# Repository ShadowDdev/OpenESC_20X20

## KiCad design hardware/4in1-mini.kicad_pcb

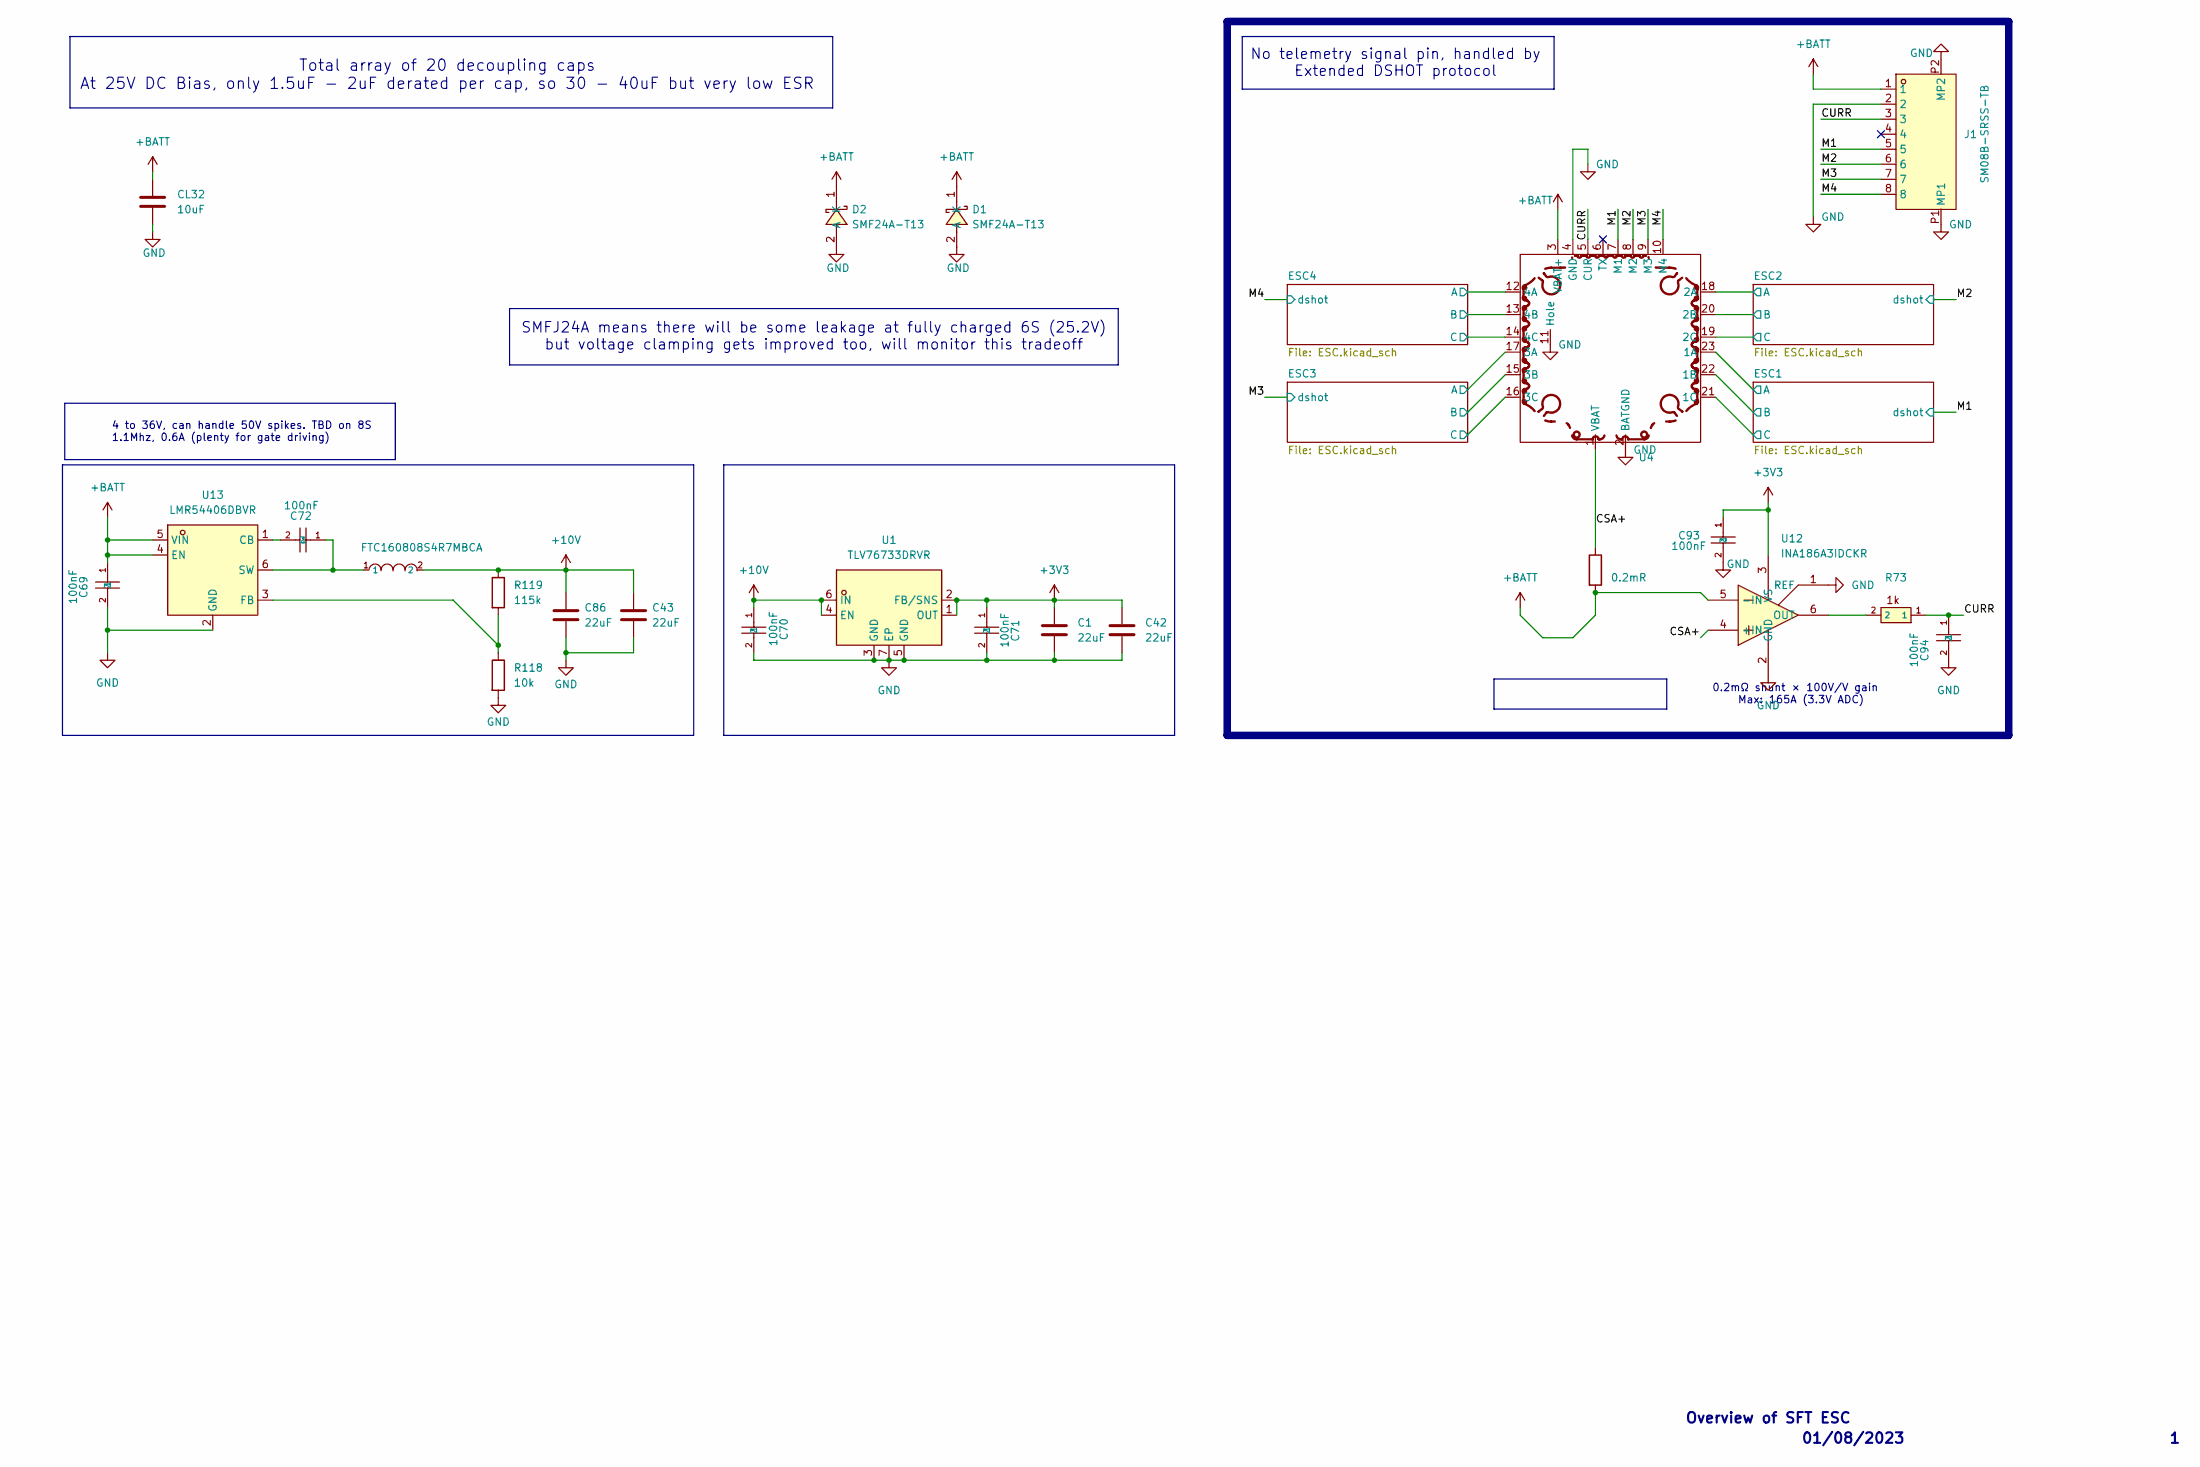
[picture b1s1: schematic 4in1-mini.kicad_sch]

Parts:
C1, C42: 22uF; C_0402_1005Metric; MPN CL05A226MQ5QUNC; LCSC C105226
C43, C86: 22uF; C_0603_1608Metric; MPN CL10A226MO7JZNC; LCSC C2762594
C69, C70, C71, C72, C93, C94: 100nF; C_0201_0603Metric; MPN GRM033R6YA104KE14D; LCSC C181043
CL32: 10uF; C_1206_3216Metric; MPN CL31B106KBHNNNE; LCSC C89632
D1, D2: SMF24A-T13; SOD-123FL_L2.7-W1.8-LS3.7-RD; MPN SMF24A-T13; LCSC Part C1977154
J1: SM08B-SRSS-TB; JST_SM08B-SRSS-TB; MPN SM08B-SRSS-TB(LF)(SN); LCSC C160407
R73: 1k; R_0201_0603Metric; MPN 0201WMF1001TEE; LCSC C270365
R118: 10k; R_0201_0603Metric; MPN RC0201FR-0710KL; LCSC C106225
R119: 115k; R_0201_0603Metric; MPN RTT011153FTH; LCSC C166378
Rsense1: 0.2mR; R_2512_6332Metric; MPN ASR-S-3-0.2F; LCSC C695806
U1: TLV76733DRVR; WSON-6_L2.0-W2.0-P0.65-TL-EP; MPN TLV76733DRVR; LCSC C2848334
U4: 4in1ESC
U5: FTC160808S4R7MBCA; IND-SMD_L1.6-W0.8_FTC160865SR47MBCA; MPN FTC160808S4R7MBCA; LCSC C46594347
U12: INA186A3IDCKR; SOT-363_SC-70-6; MPN INA186A3IDCKR; LCSC C2058245
U13: LMR54406DBVR; SOT-23-6_L2.9-W1.6-P0.95-LS2.8-BR; MPN LMR54406DBVR; LCSC Part C5219316

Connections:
+3V3: C1.2, C42.2, C71.1, C93.1, U1.1 (OUT), U1.2 (FB/SNS), U12.3 (VS); also elsewhere on the board
+10V: C43.1, C70.1, C86.1, R119.1, U1.4 (EN), U1.6 (IN), U5.2; also elsewhere on the board
+BATT: C69.1, CL32.1, D1.1 (K), D2.1 (K), J1.1, Rsense1.2, U4.3 (VBAT+), U12.5 (-IN), U13.4 (EN), U13.5 (VIN); also elsewhere on the board
/CSA+: Rsense1.1, U4.1 (VBAT), U12.4 (+IN)
/CURR: C94.1, J1.3, R73.1, U4.5 (CUR)
/ESC1/MotorA: U4.23 (1A); also elsewhere on the board
/ESC1/MotorB: U4.22 (1B); also elsewhere on the board
/ESC1/MotorC: U4.21 (1C); also elsewhere on the board
/ESC2/MotorA: U4.18 (2A); also elsewhere on the board
/ESC2/MotorB: U4.20 (2B); also elsewhere on the board
/ESC2/MotorC: U4.19 (2C); also elsewhere on the board
/ESC3/MotorA: U4.17 (3A); also elsewhere on the board
/ESC3/MotorB: U4.15 (3B); also elsewhere on the board
/ESC3/MotorC: U4.16 (3C); also elsewhere on the board
/ESC4/MotorA: U4.12 (4A); also elsewhere on the board
/ESC4/MotorB: U4.13 (4B); also elsewhere on the board
/ESC4/MotorC: U4.14 (4C); also elsewhere on the board
/M1: J1.5, U4.7 (M1); also elsewhere on the board
/M2: J1.6, U4.8 (M2); also elsewhere on the board
/M3: J1.7, U4.9 (M3); also elsewhere on the board
/M4: J1.8, U4.10 (M4); also elsewhere on the board
GND: C1.1, C42.1, C43.2, C69.2, C70.2, C71.2, C86.2, C93.2, C94.2, CL32.2, D1.2 (A), D2.2 (A), J1.2, J1.P1 (MP1), J1.P2 (MP2), R118.2, U1.3 (GND), U1.5 (GND), U1.7 (EP), U4.2 (BATGND), U4.4 (GND), U4.11 (Hole), U12.1 (REF), U12.2 (GND), U13.2 (GND); also elsewhere on the board
unnamed: R73.2, U12.6 (OUT)
unnamed: C72.2, U13.1 (CB)
unnamed: R118.1, R119.2, U13.3 (FB)
unnamed: C72.1, U5.1, U13.6 (SW)

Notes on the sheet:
01/08/2023
No telemetry signal pin, handled by Extended DSHOT protocol
4 to 36V, can handle 50V spikes. TBD on 8S 1.1Mhz, 0.6A (plenty for gate driving)
SMFJ24A means there will be some leakage at fully charged 6S (25.2V) but voltage clamping gets improved too, will monitor this tradeoff
Overview of SFT ESC
Total array of 20 decoupling caps At 25V DC Bias, only 1.5uF - 2uF derated per cap, so 30 - 40uF but very low ESR
0.2mΩ shunt × 100V/V gain Max: 165A (3.3V ADC)

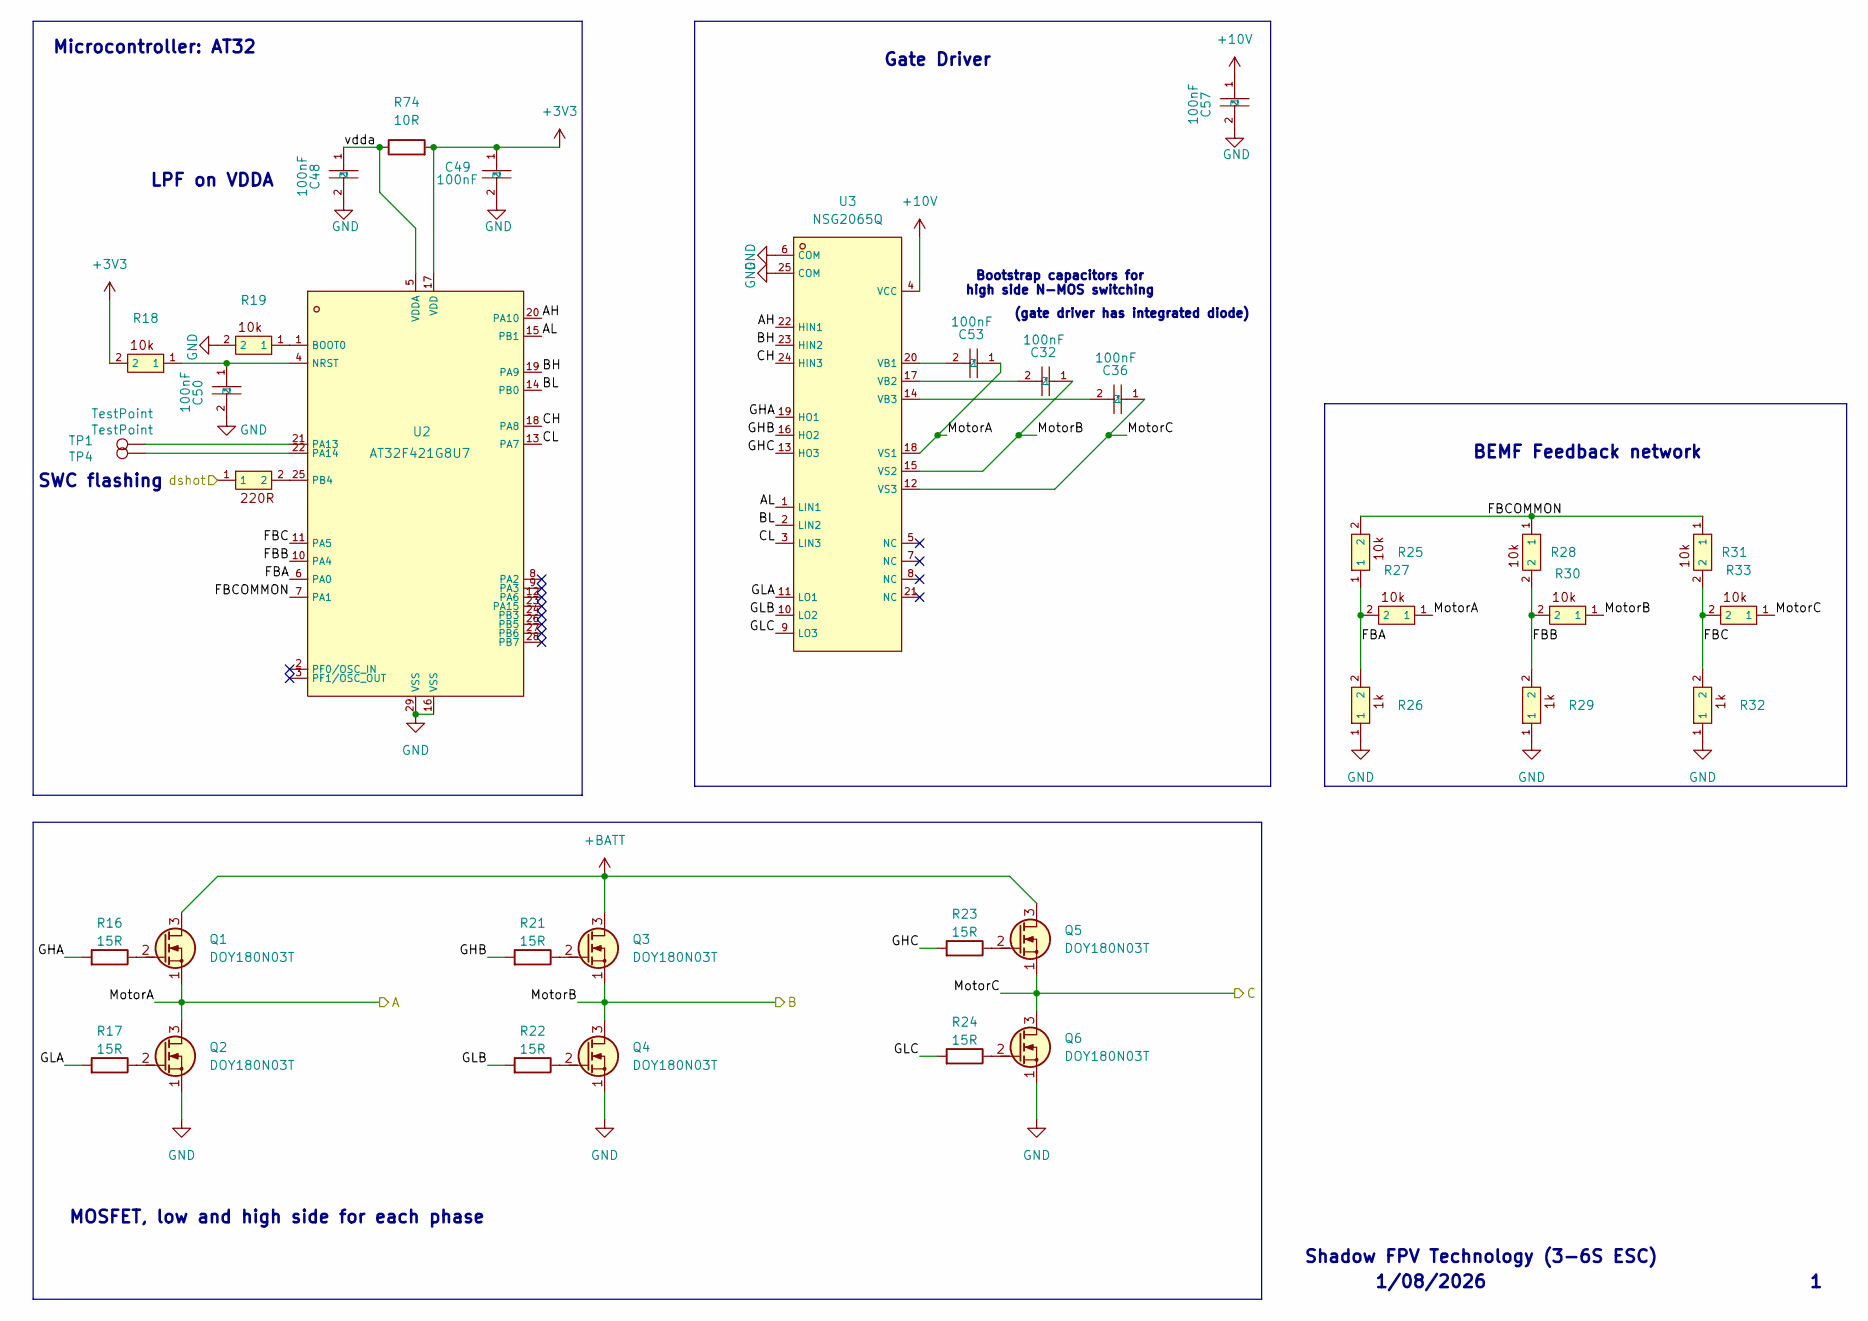
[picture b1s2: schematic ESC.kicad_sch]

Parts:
C32, C36, C53: 100nF; C_0402_WIDE; MPN CL05B104KB54PNC; LCSC C307331
C48, C49, C50, C57: 100nF; C_0201_0603Metric; MPN GRM033R6YA104KE14D; LCSC C181043
Q1, Q2, Q3, Q4, Q5, Q6: DOY180N03T; Diodes_PowerDI3333-8; MPN DOY180N03T; LCSC C49441966
R16, R17, R21, R22, R23, R24: 15R; R_0201_0603Metric; MPN 0201WMF150JTEE; LCSC C473542
R18, R19, R25, R27, R28, R30, R31, R33: 10k; R_0201_0603Metric; MPN RC0201FR-0710KL; LCSC C106225
R20: 220R; R_0201_0603Metric; MPN AC0201FR-07220RL; LCSC C226468
R26, R29, R32: 1k; R_0201_0603Metric; MPN 0201WMF1001TEE; LCSC C270365
R74: 10R; R_0201_0603Metric; MPN RC0201FR-0710RL; LCSC C106226
TP1, TP4: TestPoint; TestPoint_Pad_D1.0mm
U2: AT32F421G8U7; QFN-28_L4.0-W4.0-P0.40-TL-EP2.4; MPN AT32F421G8U7; LCSC C2765098
U3: NSG2065Q; QFN-24_L4.0-W4.0-P0.50-TL-EP2.8; MPN NSG2065Q; LCSC C41414478

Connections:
+3V3: C49.1, R18.2, R74.2, U2.17 (VDD); also elsewhere on the board
+10V: C57.1, U3.4 (VCC); also elsewhere on the board
+BATT: Q1.3 (D), Q3.3 (D), Q5.3 (D); also elsewhere on the board
/ESC1/AH: U2.20 (PA10), U3.22 (HIN1)
/ESC1/AL: U2.15 (PB1), U3.1 (LIN1)
/ESC1/BH: U2.19 (PA9), U3.23 (HIN2)
/ESC1/BL: U2.14 (PB0), U3.2 (LIN2)
/ESC1/CH: U2.18 (PA8), U3.24 (HIN3)
/ESC1/CL: U2.13 (PA7), U3.3 (LIN3)
/ESC1/FBA: R25.1, R26.2, R27.2, U2.6 (PA0)
/ESC1/FBB: R28.2, R29.2, R30.2, U2.10 (PA4)
/ESC1/FBC: R31.2, R32.2, R33.2, U2.11 (PA5)
/ESC1/FBCOMMON: R25.2, R28.1, R31.1, U2.7 (PA1)
/ESC1/GHA: R16.1, U3.19 (HO1)
/ESC1/GHB: R21.1, U3.16 (HO2)
/ESC1/GHC: R23.1, U3.13 (HO3)
/ESC1/GLA: R17.1, U3.11 (LO1)
/ESC1/GLB: R22.1, U3.10 (LO2)
/ESC1/GLC: R24.1, U3.9 (LO3)
/ESC1/MotorA: C53.1, Q1.1 (S), Q2.3 (D), R27.1, U3.18 (VS1); also elsewhere on the board
/ESC1/MotorB: C32.1, Q3.1 (S), Q4.3 (D), R30.1, U3.15 (VS2); also elsewhere on the board
/ESC1/MotorC: C36.1, Q5.1 (S), Q6.3 (D), R33.1, U3.12 (VS3); also elsewhere on the board
/ESC1/vdda: C48.1, R74.1, U2.5 (VDDA)
/M1: R20.1; also elsewhere on the board
GND: C48.2, C49.2, C50.2, C57.2, Q2.1 (S), Q4.1 (S), Q6.1 (S), R19.2, R26.1, R29.1, R32.1, U2.16 (VSS), U2.29 (VSS), U3.6 (COM), U3.25 (COM); also elsewhere on the board
unnamed: Q1.2 (G), R16.2
unnamed: Q2.2 (G), R17.2
unnamed: Q3.2 (G), R21.2
unnamed: Q4.2 (G), R22.2
unnamed: Q5.2 (G), R23.2
unnamed: Q6.2 (G), R24.2
unnamed: R19.1, U2.1 (BOOT0)
unnamed: C50.1, R18.1, U2.4 (NRST)
unnamed: TP1.1 (1_1), U2.21 (PA13)
unnamed: TP4.1 (1_1), U2.22 (PA14)
unnamed: R20.2, U2.25 (PB4)
unnamed: C53.2, U3.20 (VB1)
unnamed: C32.2, U3.17 (VB2)
unnamed: C36.2, U3.14 (VB3)

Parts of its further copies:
C33, C34, C35, C37, C38, C39, C59, C73, C83: 100nF; C_0402_WIDE; MPN CL05B104KB54PNC; LCSC C307331
C44, C45, C46, C63, C64, C65, C66, C77, C78, C79, C80, C88: 100nF; C_0201_0603Metric; MPN GRM033R6YA104KE14D; LCSC C181043
Q7, Q8, Q9, Q10, Q11, Q12, Q13, Q14, Q15, Q16, Q17, Q18, Q19, Q20, Q21, Q22, Q23, Q24: DOY180N03T; Diodes_PowerDI3333-8; MPN DOY180N03T; LCSC C49441966
R1, R2, R6, R7, R8, R9, R37, R38, R42, R43, R44, R45, R55, R56, R60, R61, R62, R63: 15R; R_0201_0603Metric; MPN 0201WMF150JTEE; LCSC C473542
R3, R4, R10, R12, R13, R15, R34, R36, R39, R40, R46, R48, R49, R51, R52, R54, R57, R58, R64, R66, R67, R69, R70, R72: 10k; R_0201_0603Metric; MPN RC0201FR-0710KL; LCSC C106225
R5, R41, R59: 220R; R_0201_0603Metric; MPN AC0201FR-07220RL; LCSC C226468
R11, R14, R35, R47, R50, R53, R65, R68, R71: 1k; R_0201_0603Metric; MPN 0201WMF1001TEE; LCSC C270365
R75, R76, R77: 10R; R_0201_0603Metric; MPN RC0201FR-0710RL; LCSC C106226
TP2, TP3, TP5, TP6, TP7, TP8: TestPoint; TestPoint_Pad_D1.0mm
U6, U8, U10: AT32F421G8U7; QFN-28_L4.0-W4.0-P0.40-TL-EP2.4; MPN AT32F421G8U7; LCSC C2765098
U7, U9, U11: NSG2065Q; QFN-24_L4.0-W4.0-P0.50-TL-EP2.8; MPN NSG2065Q; LCSC C41414478

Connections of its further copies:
+3V3: C45.1, C65.1, C79.1, R3.2, R39.2, R57.2, R75.2, R76.2, R77.2, U6.17 (VDD), U8.17 (VDD), U10.17 (VDD); also elsewhere on the board
+10V: C63.1, C77.1, C88.1, U7.4 (VCC), U9.4 (VCC), U11.4 (VCC); also elsewhere on the board
+BATT: Q7.3 (D), Q9.3 (D), Q11.3 (D), Q13.3 (D), Q15.3 (D), Q17.3 (D), Q19.3 (D), Q21.3 (D), Q23.3 (D); also elsewhere on the board
/ESC2/AH: U6.20 (PA10), U7.22 (HIN1)
/ESC2/AL: U6.15 (PB1), U7.1 (LIN1)
/ESC2/BH: U6.19 (PA9), U7.23 (HIN2)
/ESC2/BL: U6.14 (PB0), U7.2 (LIN2)
/ESC2/CH: U6.18 (PA8), U7.24 (HIN3)
/ESC2/CL: U6.13 (PA7), U7.3 (LIN3)
/ESC2/FBA: R10.1, R11.2, R12.2, U6.6 (PA0)
/ESC2/FBB: R13.2, R14.2, R15.2, U6.10 (PA4)
/ESC2/FBC: R34.2, R35.2, R36.2, U6.11 (PA5)
/ESC2/FBCOMMON: R10.2, R13.1, R34.1, U6.7 (PA1)
/ESC2/GHA: R1.1, U7.19 (HO1)
/ESC2/GHB: R6.1, U7.16 (HO2)
/ESC2/GHC: R8.1, U7.13 (HO3)
/ESC2/GLA: R2.1, U7.11 (LO1)
/ESC2/GLB: R7.1, U7.10 (LO2)
/ESC2/GLC: R9.1, U7.9 (LO3)
/ESC2/MotorA: C59.1, Q7.1 (S), Q8.3 (D), R12.1, U7.18 (VS1); also elsewhere on the board
/ESC2/MotorB: C33.1, Q9.1 (S), Q10.3 (D), R15.1, U7.15 (VS2); also elsewhere on the board
/ESC2/MotorC: C37.1, Q11.1 (S), Q12.3 (D), R36.1, U7.12 (VS3); also elsewhere on the board
/ESC2/vdda: C44.1, R75.1, U6.5 (VDDA)
/ESC3/AH: U8.20 (PA10), U9.22 (HIN1)
/ESC3/AL: U8.15 (PB1), U9.1 (LIN1)
/ESC3/BH: U8.19 (PA9), U9.23 (HIN2)
/ESC3/BL: U8.14 (PB0), U9.2 (LIN2)
/ESC3/CH: U8.18 (PA8), U9.24 (HIN3)
/ESC3/CL: U8.13 (PA7), U9.3 (LIN3)
/ESC3/FBA: R46.1, R47.2, R48.2, U8.6 (PA0)
/ESC3/FBB: R49.2, R50.2, R51.2, U8.10 (PA4)
/ESC3/FBC: R52.2, R53.2, R54.2, U8.11 (PA5)
/ESC3/FBCOMMON: R46.2, R49.1, R52.1, U8.7 (PA1)
/ESC3/GHA: R37.1, U9.19 (HO1)
/ESC3/GHB: R42.1, U9.16 (HO2)
/ESC3/GHC: R44.1, U9.13 (HO3)
/ESC3/GLA: R38.1, U9.11 (LO1)
/ESC3/GLB: R43.1, U9.10 (LO2)
/ESC3/GLC: R45.1, U9.9 (LO3)
/ESC3/MotorA: C73.1, Q13.1 (S), Q14.3 (D), R48.1, U9.18 (VS1); also elsewhere on the board
/ESC3/MotorB: C34.1, Q15.1 (S), Q16.3 (D), R51.1, U9.15 (VS2); also elsewhere on the board
/ESC3/MotorC: C38.1, Q17.1 (S), Q18.3 (D), R54.1, U9.12 (VS3); also elsewhere on the board
/ESC3/vdda: C64.1, R76.1, U8.5 (VDDA)
/ESC4/AH: U10.20 (PA10), U11.22 (HIN1)
/ESC4/AL: U10.15 (PB1), U11.1 (LIN1)
/ESC4/BH: U10.19 (PA9), U11.23 (HIN2)
/ESC4/BL: U10.14 (PB0), U11.2 (LIN2)
/ESC4/CH: U10.18 (PA8), U11.24 (HIN3)
/ESC4/CL: U10.13 (PA7), U11.3 (LIN3)
/ESC4/FBA: R64.1, R65.2, R66.2, U10.6 (PA0)
/ESC4/FBB: R67.2, R68.2, R69.2, U10.10 (PA4)
/ESC4/FBC: R70.2, R71.2, R72.2, U10.11 (PA5)
/ESC4/FBCOMMON: R64.2, R67.1, R70.1, U10.7 (PA1)
/ESC4/GHA: R55.1, U11.19 (HO1)
/ESC4/GHB: R60.1, U11.16 (HO2)
/ESC4/GHC: R62.1, U11.13 (HO3)
/ESC4/GLA: R56.1, U11.11 (LO1)
/ESC4/GLB: R61.1, U11.10 (LO2)
/ESC4/GLC: R63.1, U11.9 (LO3)
/ESC4/MotorA: C83.1, Q19.1 (S), Q20.3 (D), R66.1, U11.18 (VS1); also elsewhere on the board
/ESC4/MotorB: C35.1, Q21.1 (S), Q22.3 (D), R69.1, U11.15 (VS2); also elsewhere on the board
/ESC4/MotorC: C39.1, Q23.1 (S), Q24.3 (D), R72.1, U11.12 (VS3); also elsewhere on the board
/ESC4/vdda: C78.1, R77.1, U10.5 (VDDA)
/M2: R5.1; also elsewhere on the board
/M3: R41.1; also elsewhere on the board
/M4: R59.1; also elsewhere on the board
GND: C44.2, C45.2, C46.2, C63.2, C64.2, C65.2, C66.2, C77.2, C78.2, C79.2, C80.2, C88.2, Q8.1 (S), Q10.1 (S), Q12.1 (S), Q14.1 (S), Q16.1 (S), Q18.1 (S), Q20.1 (S), Q22.1 (S), Q24.1 (S), R4.2, R11.1, R14.1, R35.1, R40.2, R47.1, R50.1, R53.1, R58.2, R65.1, R68.1, R71.1, U6.16 (VSS), U6.29 (VSS), U7.6 (COM), U7.25 (COM), U8.16 (VSS), U8.29 (VSS), U9.6 (COM), U9.25 (COM), U10.16 (VSS), U10.29 (VSS), U11.6 (COM), U11.25 (COM); also elsewhere on the board
unnamed: Q7.2 (G), R1.2
unnamed: Q8.2 (G), R2.2
unnamed: Q9.2 (G), R6.2
unnamed: Q10.2 (G), R7.2
unnamed: Q11.2 (G), R8.2
unnamed: Q12.2 (G), R9.2
unnamed: Q13.2 (G), R37.2
unnamed: Q14.2 (G), R38.2
unnamed: Q15.2 (G), R42.2
unnamed: Q16.2 (G), R43.2
unnamed: Q17.2 (G), R44.2
unnamed: Q18.2 (G), R45.2
unnamed: Q19.2 (G), R55.2
unnamed: Q20.2 (G), R56.2
unnamed: Q21.2 (G), R60.2
unnamed: Q22.2 (G), R61.2
unnamed: Q23.2 (G), R62.2
unnamed: Q24.2 (G), R63.2
unnamed: R4.1, U6.1 (BOOT0)
unnamed: C46.1, R3.1, U6.4 (NRST)
unnamed: TP2.1 (1_1), U6.21 (PA13)
unnamed: TP3.1 (1_1), U6.22 (PA14)
unnamed: R5.2, U6.25 (PB4)
unnamed: C59.2, U7.20 (VB1)
unnamed: C33.2, U7.17 (VB2)
unnamed: C37.2, U7.14 (VB3)
unnamed: R40.1, U8.1 (BOOT0)
unnamed: C66.1, R39.1, U8.4 (NRST)
unnamed: TP5.1 (1_1), U8.21 (PA13)
unnamed: TP6.1 (1_1), U8.22 (PA14)
unnamed: R41.2, U8.25 (PB4)
unnamed: C73.2, U9.20 (VB1)
unnamed: C34.2, U9.17 (VB2)
unnamed: C38.2, U9.14 (VB3)
unnamed: R58.1, U10.1 (BOOT0)
unnamed: C80.1, R57.1, U10.4 (NRST)
unnamed: TP7.1 (1_1), U10.21 (PA13)
unnamed: TP8.1 (1_1), U10.22 (PA14)
unnamed: R59.2, U10.25 (PB4)
unnamed: C83.2, U11.20 (VB1)
unnamed: C35.2, U11.17 (VB2)
unnamed: C39.2, U11.14 (VB3)

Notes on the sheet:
Bootstrap capacitors for high side N-MOS switching
Gate Driver
MOSFET, low and high side for each phase
Shadow FPV Technology (3-6S ESC)
Microcontroller: AT32
SWC flashing
(gate driver has integrated diode)
1/08/2026
BEMF Feedback network
LPF on VDDA

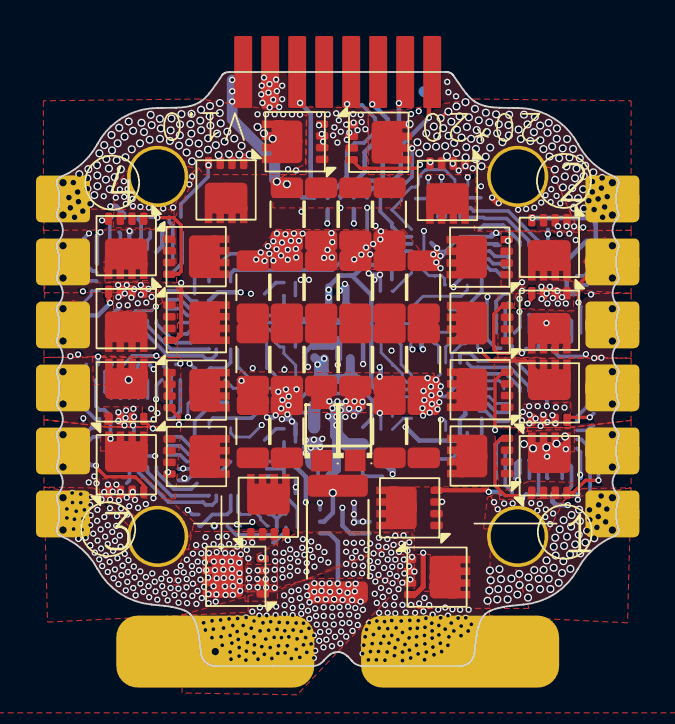
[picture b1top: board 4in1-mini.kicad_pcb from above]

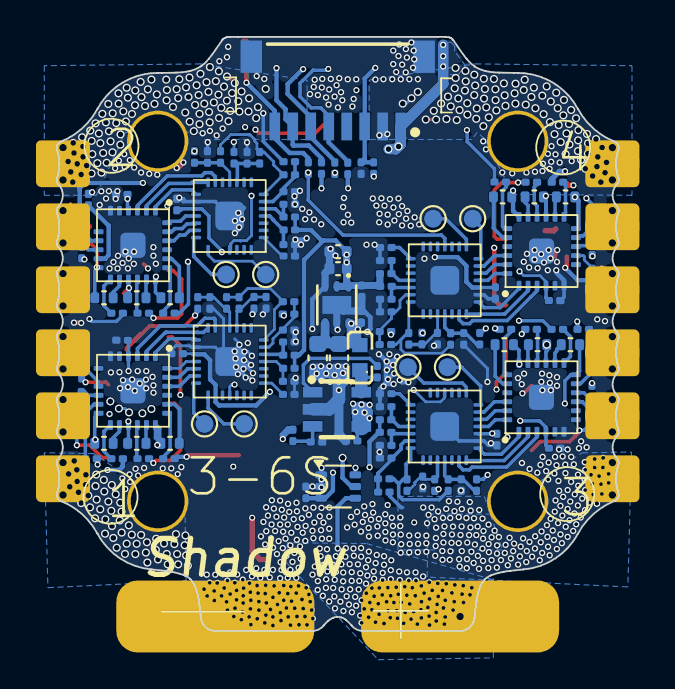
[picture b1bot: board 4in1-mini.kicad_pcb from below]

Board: 6 copper layers, 31.2 x 33.0 mm, 186 parts (138 on the bottom side), 150 nets.

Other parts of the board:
CL33, CL34, CL35, CL36, CL38, CL39, CL40, CL42, CL43, CL44, CL45, CL46, CL47, CL48, CL49, CL50, CL51, CL54, CL55: 10uF; C_1206_3216Metric

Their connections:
+BATT: CL33.1, CL34.1, CL35.1, CL36.1, CL38.1, CL39.1, CL40.1, CL42.1, CL43.1, CL44.1, CL45.1, CL46.1, CL47.1, CL48.1, CL49.1, CL50.1, CL51.1, CL54.1, CL55.1; also elsewhere on the board
GND: CL33.2, CL34.2, CL35.2, CL36.2, CL38.2, CL39.2, CL40.2, CL42.2, CL43.2, CL44.2, CL45.2, CL46.2, CL47.2, CL48.2, CL49.2, CL50.2, CL51.2, CL54.2, CL55.2; also elsewhere on the board
